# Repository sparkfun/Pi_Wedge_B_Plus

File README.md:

**NOTE:** *This product has been retired from our catalog. For the latest version, check out [BOB-13717](https://www.sparkfun.com/products/13717).*

*If you are looking for more up-to-date info, please check out some of these resources to see how other users are still hacking and improving on this version of the product.*
* *[SparkFun Forum](https://forum.sparkfun.com/)*
* *[Comments Here on GitHub](https://github.com/sparkfun/Pi_Wedge_B_Plus/issues)*
* *[IRC Channel](https://www.sparkfun.com/news/263)*

Pi Wedge B Plus - Breakout For Raspberry Pi B+ GPIO Connector
----------------------------

_Syntactic note: Guthub didn't like the '+' character in the name, so it's spelled out, instead._ 

----------------------------

This is the Pi Wedge B Plus, a board that connects to the Raspberry Pi B+’s 40-pin GPIO connector, and breaks the pins out to breadboard-friendly arrangement and spacing, and even adds a couple of decoupling capacitors on the power supply lines. The “Wedge” also makes the initial bringup process easier - you can plug an FTDI Basic module into the built-in serial port. Each Pi Wedge comes as an easy to assemble kit that can can be inserted into the Raspberry Pi’s GPIO port that allows you to prototype as soon as you are done soldering.

The kit works with both the Model A+ and [Model B+](https://www.sparkfun.com/products/11546) versions of the Raspberry Pi.

For the Model A and Model B, we also offer the regular [Pi Wedge](https://www.sparkfun.com/products/12652) 

It adapts the GPIO header on the B+ to a standard solderless breadboard, such as our [meduim](https://www.sparkfun.com/products/12002), [large](https://www.sparkfun.com/products/112) and [extra large](https://www.sparkfun.com/products/12614) breadboards.  While it will technically with with a [mini](https://www.sparkfun.com/products/12043) breadboard, it won't leave much room for external circuitry.

More information can be found on the [Pi Wedge B+ product Page](https://www.sparkfun.com/products/12994), and in the [Pi Wedge B+ hookup guide](https://learn.sparkfun.com/tutorials/pi-wedge-b-hookup-guide).

This part was created in Eagle v6.5.0.  Software examples were developed using the [WiringPi](wiringpi.com) libraries and utilities.

Repository Contents
-------------------

* **/Hardware** - All Eagle design files (.brd, .sch, .STL)
* **/Software** - C source code for SPI, I2C and GPIO examples.  All use [WiringPi](wiringpi.com) for the underlying device interfaces

Documentation
--------------

* **[Hookup Guide](https://learn.sparkfun.com/tutorials/retired---pi-wedge-b-hookup-guide)** - Basic hookup guide
* **[Raspberry gPIo](https://learn.sparkfun.com/tutorials/raspberry-gpio)** - Programming guide using the Pi's I/O pins with Python and C. 
* **[Raspberry Pi SPI and I2C Tutorial](https://learn.sparkfun.com/tutorials/raspberry-pi-spi-and-i2c-tutorial)** - Programming guide using the Pi's SPI and I2C.

Product Versions
----------------
* [V1.1](https://www.sparkfun.com/products/retired/13091)- Pi Wedge B+ kit

Version History
---------------

* [820b901aa31b3c76c1dbefd9966a04860c9f83ca](https://github.com/sparkfun/Pi_Wedge_B_Plus/commit/820b901aa31b3c76c1dbefd9966a04860c9f83ca) - Initial release version.

License Information
-------------------
The hardware is released under [Creative Commons ShareAlike 4.0 International](https://creativecommons.org/licenses/by-sa/4.0/).

The code is beerware; if you see me (or any other SparkFun employee) at the local, and you've found our code helpful, please buy us a round!

Distributed as-is; no warranty is given.

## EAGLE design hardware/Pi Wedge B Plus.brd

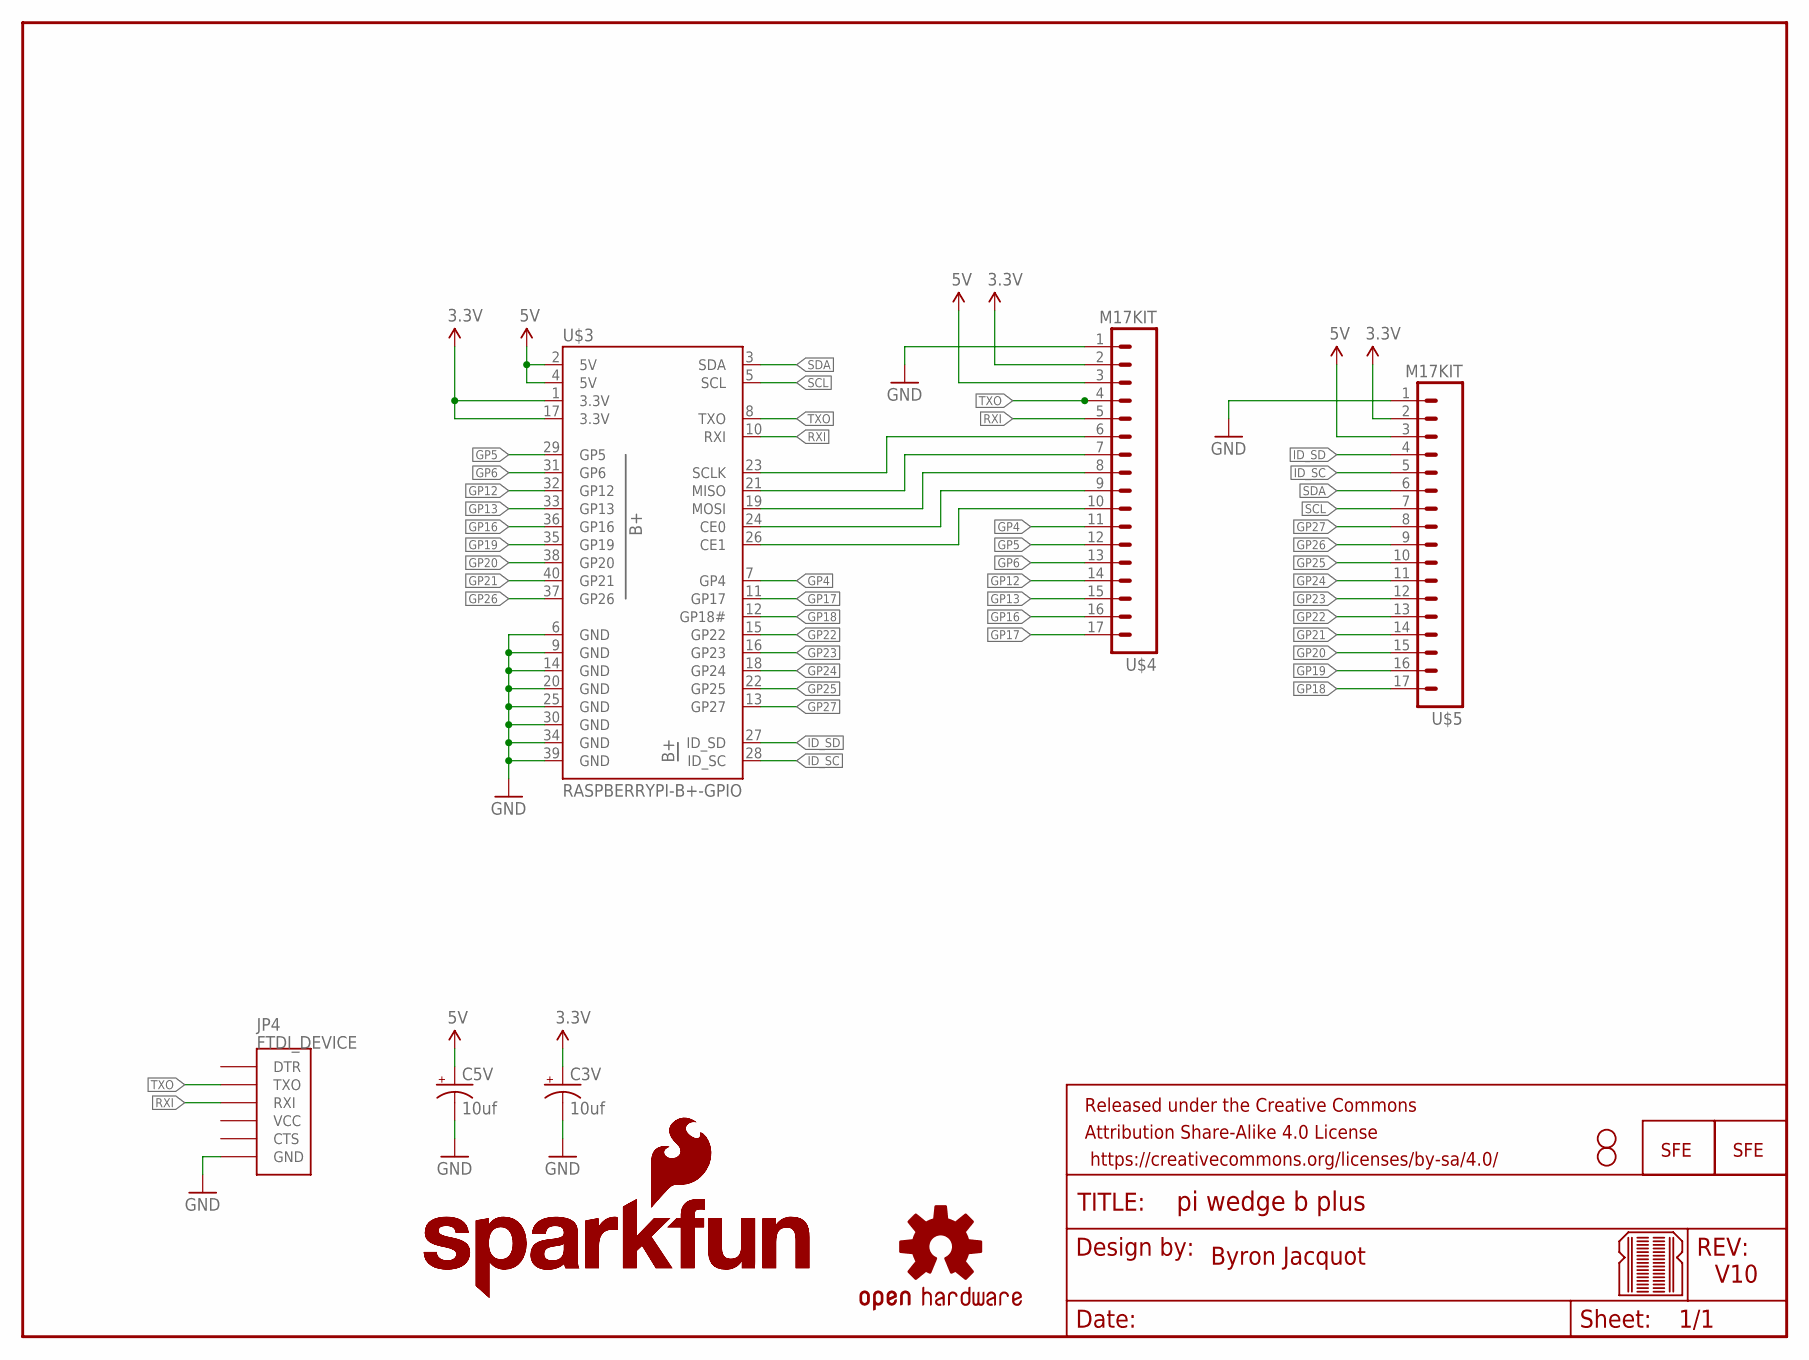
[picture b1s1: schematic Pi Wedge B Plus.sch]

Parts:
C3V, C5V: 10uf; CPOL-RADIAL-10UF-25V-KIT
FRAME2: FRAME-LETTER; CREATIVE_COMMONS
JP1, JP5: LOGO-SFESK; SFE-LOGO-FLAME
JP4: FTDI_DEVICE; FTDI_DEVICE_SIDE
LOGO1, LOGO2: SFE_LOGO_NAME_FLAME.2_INCH; SFE_LOGO_NAME_FLAME_.2
STANDOFF1, STANDOFF2: STAND-OFF
U$1: OSHW-LOGOS; OSHW-LOGO-S
U$2: BREADBOARD_PATTERN; BREADBOARD_SPACING
U$3: RASPBERRYPI-B+-GPIO; 2X20-SHROUDED
U$4, U$5: M17KIT; 1X17_NO_SILK_KIT

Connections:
3.3V: C3V.1 (+), U$3.1 (3.3V), U$3.17 (3.3V), U$4.2, U$5.2
5V: C5V.1 (+), U$3.2 (5V), U$3.4 (5V), U$4.3, U$5.3
CE0: U$3.24 (CE0), U$4.9
CE1: U$3.26 (CE1), U$4.10
GND: C3V.2 (-), C5V.2 (-), JP4.P$6 (GND), U$3.6 (GND), U$3.9 (GND), U$3.14 (GND), U$3.20 (GND), U$3.25 (GND), U$3.30 (GND), U$3.34 (GND), U$3.39 (GND), U$4.1, U$5.1
GP4: U$3.7 (GP4), U$4.11
GP5: U$3.29 (GP5), U$4.12
GP6: U$3.31 (GP6), U$4.13
GP12: U$3.32 (GP12), U$4.14
GP13: U$3.33 (GP13), U$4.15
GP16: U$3.36 (GP16), U$4.16
GP17: U$3.11 (GP17), U$4.17
GP18: U$3.12 (GP18#), U$5.17
GP19: U$3.35 (GP19), U$5.16
GP20: U$3.38 (GP20), U$5.15
GP21: U$3.40 (GP21), U$5.14
GP22: U$3.15 (GP22), U$5.13
GP23: U$3.16 (GP23), U$5.12
GP24: U$3.18 (GP24), U$5.11
GP25: U$3.22 (GP25), U$5.10
GP26: U$3.37 (GP26), U$5.9
GP27: U$3.13 (GP27), U$5.8
ID_SC: U$3.28 (ID_SC), U$5.5
ID_SD: U$3.27 (ID_SD), U$5.4
MISO: U$3.21 (MISO), U$4.7
MOSI: U$3.19 (MOSI), U$4.8
RXI: JP4.P$3 (RXI), U$3.10 (RXI), U$4.5
SCL: U$3.5 (SCL), U$5.7
SCLK: U$3.23 (SCLK), U$4.6
SDA: U$3.3 (SDA), U$5.6
TXO: JP4.P$2 (TXO), U$3.8 (TXO), U$4.4

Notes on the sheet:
Byron Jacquot
V10

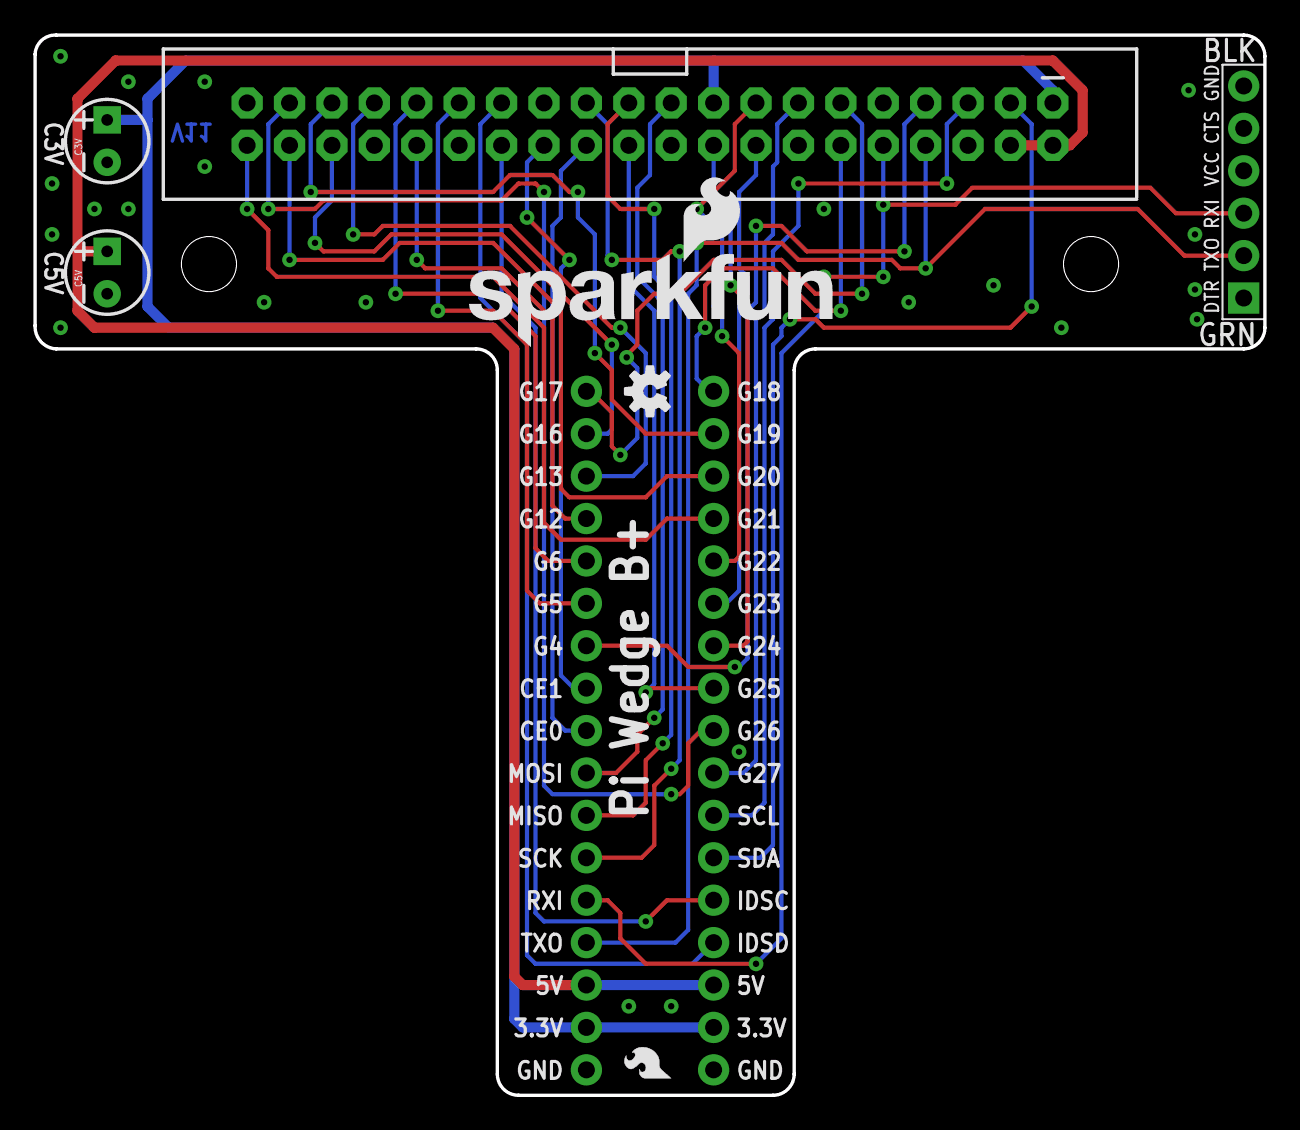
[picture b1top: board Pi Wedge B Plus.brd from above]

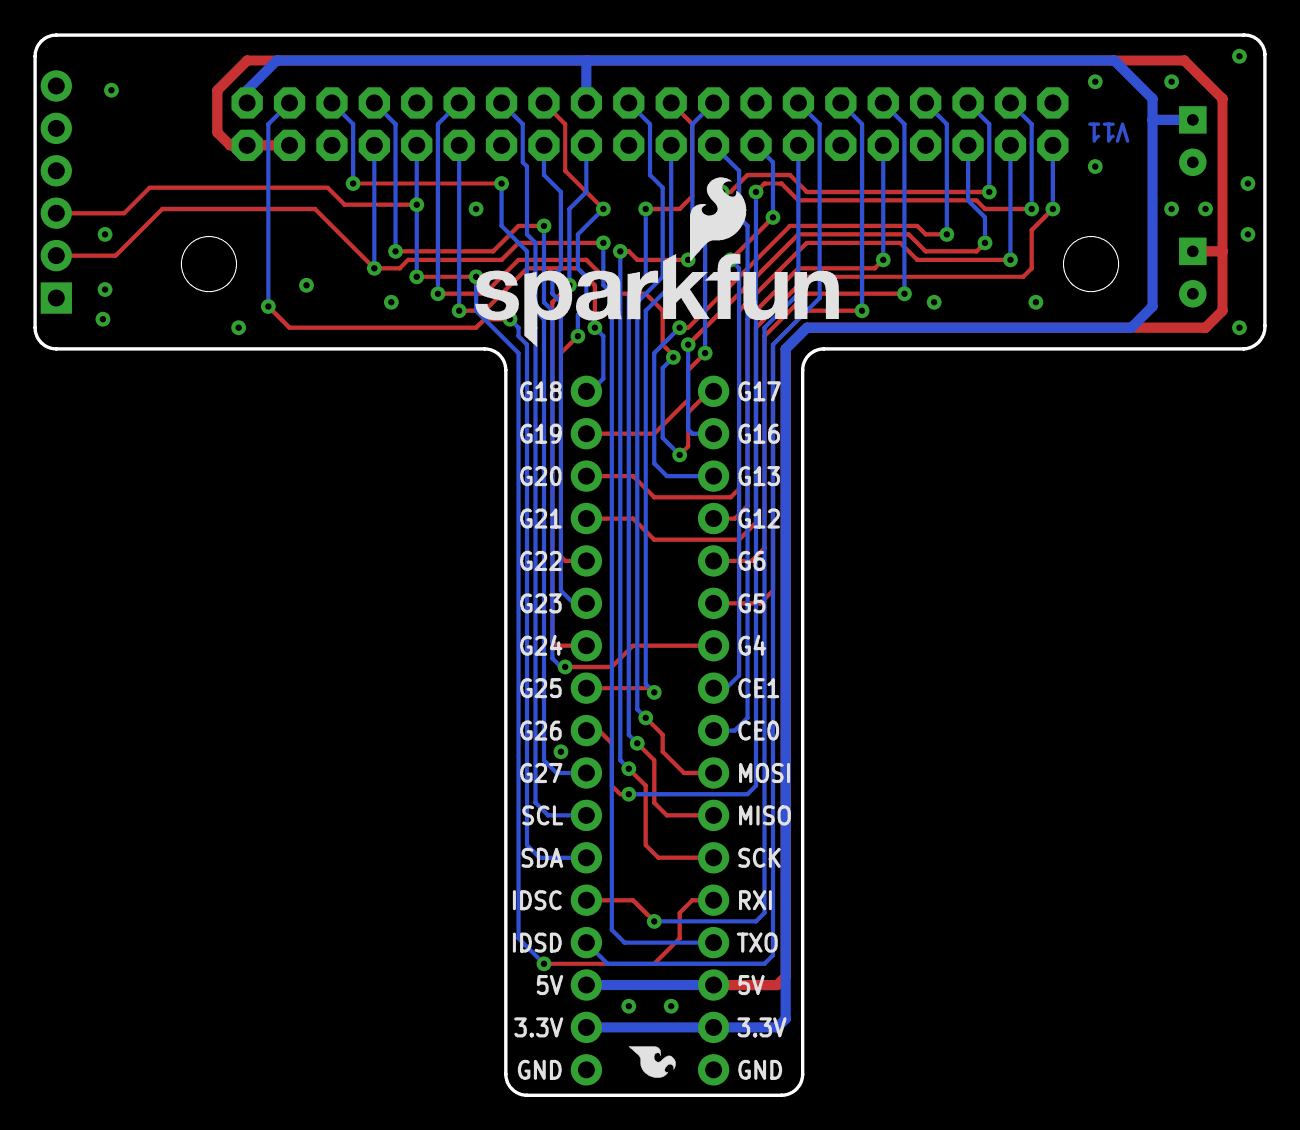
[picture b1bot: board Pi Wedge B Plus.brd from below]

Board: 2 copper layers, 73.7 x 63.5 mm, 15 parts (4 on the bottom side), 31 nets.

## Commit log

2014-08-22 Initial commit
    Mostly copied from old Pi Wedge repo
2014-08-26 Better routing.
2014-08-27 Slight Tweaks to outline
2014-10-06 Bumping rev number for reds
    From V01 to V10.
2014-10-27 Fixing kit soldermask on 17-pin headers.
2014-10-27 Review updates
    Based on Pete Lewis's comments.
2014-12-18 Software updates
    Updating for extended pins on B+.
2014-12-18 Updating readme.md
    Filling in photos and links.
2014-12-18 Renaming files.
    Prepending "SparkFun_" on PCB and software files.
2016-09-20 Adding retirement note to README

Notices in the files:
parts and their libraries:
SparkFun-Connectors: Licensing: CC v3.0 Share-Alike You are welcome to use this library for commercial purposes.
SparkFun-Aesthetics: Released under the Creative Commons Attribution Share-Alike 4.0 License
SparkFun-Aesthetics: Released under the Creative Commons
